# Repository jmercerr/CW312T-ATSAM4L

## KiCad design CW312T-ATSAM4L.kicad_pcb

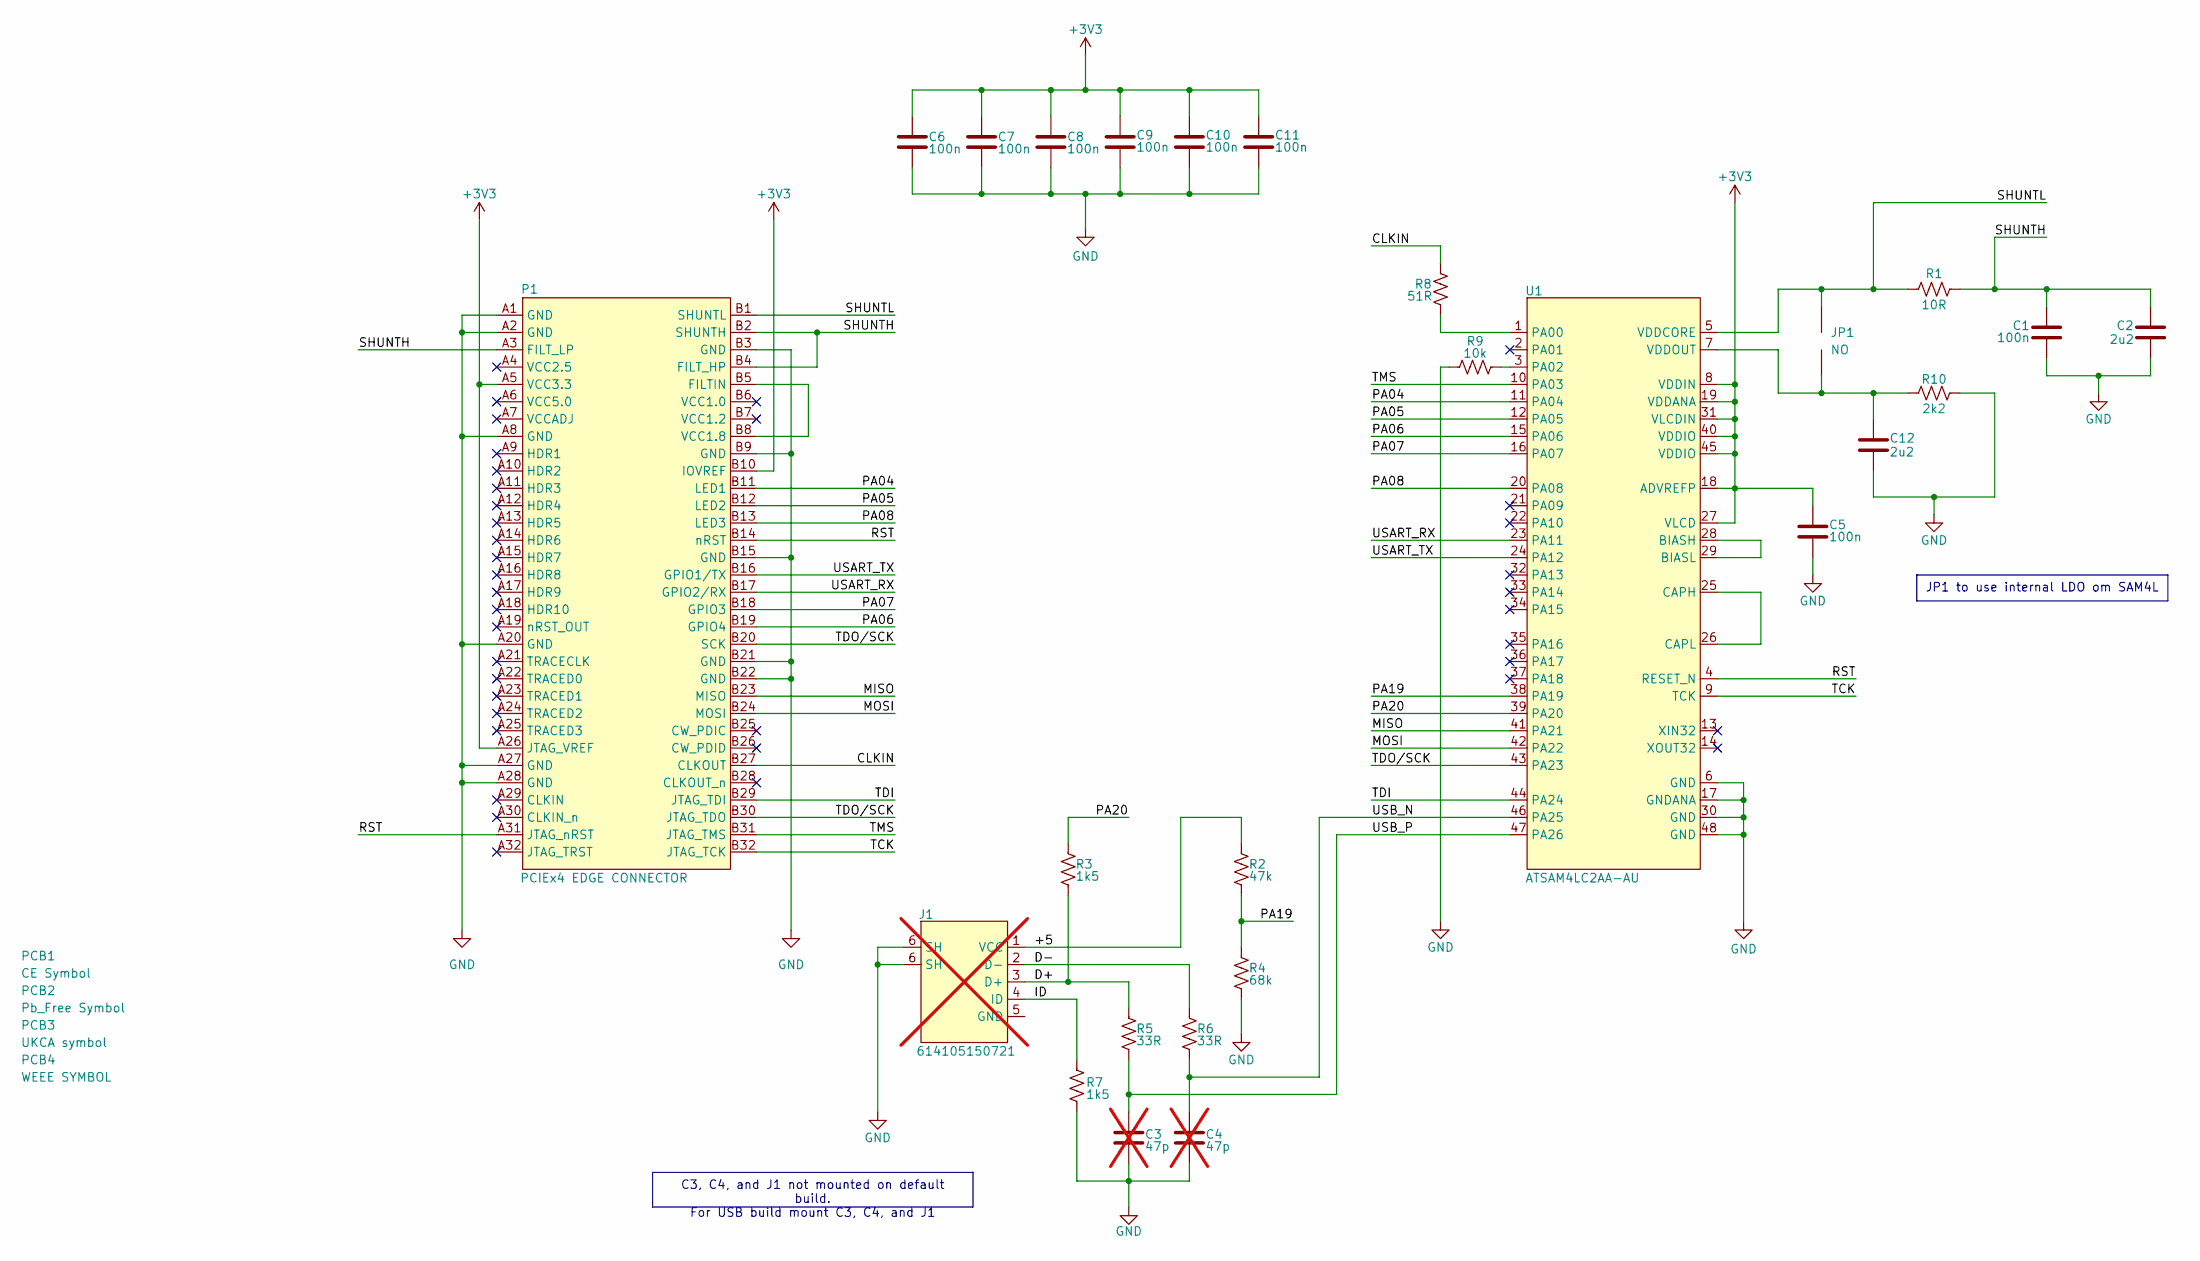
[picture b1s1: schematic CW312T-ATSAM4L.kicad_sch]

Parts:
C1, C5, C6, C7, C8, C9, C10, C11: CAP_100n_10V_0603; C_0603_1608Metric; Manufacturer Part Number CC0603KRX7R6BB104
C2, C12: CAP_2u2_6.3V_0603; C_0603_1608Metric; Manufacturer Part Number CC0603KRX7R5BB225
C3, C4: CAP_47p_50V_0603; C_0603_1608Metric; Manufacturer Part Number CC0603JRNPO9BN470; not fitted
J1: 614105150721; USB_Micro-B_Wuerth_614105150721_Vertical; Manufacturer Part Number 614105150721; not fitted
JP1: SolderJumper-2_P1.3mm_Open_Pad1.0x1.5mm
P1: PCIEx4 EDGE CONNECTOR; CW312_Template
PCB1: CE Symbol; CE-Logo_8.5x6mm_SilkScreen
PCB2: Pb_Free Symbol; Pb_Free_8.0x8.0mm_SilkScreen
PCB3: UKCA symbol; UKCA-Logo_8x8mm_SilkScreen
PCB4: WEEE SYMBOL; WEEE-Logo_5.6x8mm_SilkScreen
R1: RES_10R_0603; R_0603_1608Metric; Manufacturer Part Number RC0603FR-0710RL
R2: RES_47k_0603; R_0603_1608Metric; Manufacturer Part Number RC0603FR-0747KL
R3, R7: RES_1k5_0603; R_0603_1608Metric; Manufacturer Part Number RC0603FR-071K5L
R4: RES_68k_0603; R_0603_1608Metric; Manufacturer Part Number RC0603FR-0768KL
R5, R6: RES_33R_0603; R_0603_1608Metric; Manufacturer Part Number RC0603FR-0733RL
R8: RES_51R_0603; R_0603_1608Metric; Manufacturer Part Number RC0603FR-0751RL
R9: RES_10k_0603; R_0603_1608Metric; Manufacturer Part Number RC0603FR-0710KL
R10: RES_2k2_0603; R_0603_1608Metric; Manufacturer Part Number RC0603FR-072K2L
U1: ATSAM4LC2AA-AU; LQFP-48_7x7mm_P0.5mm; Manufacturer Part Number ATSAM4LC2AA-AU

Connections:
+3V3: C5.2, C6.2, C7.2, C8.2, C9.2, C10.2, C11.2, P1.A5 (VCC3.3), P1.A26 (JTAG_VREF), P1.B10 (IOVREF), U1.8 (VDDIN), U1.18 (ADVREFP), U1.19 (VDDANA), U1.27 (VLCD), U1.31 (VLCDIN), U1.40 (VDDIO), U1.45 (VDDIO)
/+5: J1.1 (VCC), R2.2
/CLKIN: P1.B27 (CLKOUT), R8.2
/D+: J1.3 (D+), R3.1, R5.2
/D-: J1.2 (D-), R6.2
/ID: J1.4 (ID), R7.2
/MISO: P1.B23 (MISO), U1.41 (PA21)
/MOSI: P1.B24 (MOSI), U1.42 (PA22)
/PA04: P1.B11 (LED1), U1.11 (PA04)
/PA05: P1.B12 (LED2), U1.12 (PA05)
/PA06: P1.B19 (GPIO4), U1.15 (PA06)
/PA07: P1.B18 (GPIO3), U1.16 (PA07)
/PA08: P1.B13 (LED3), U1.20 (PA08)
/PA19: R2.1, R4.2, U1.38 (PA19)
/PA20: R3.2, U1.39 (PA20)
/RST: P1.A31 (JTAG_nRST), P1.B14 (nRST), U1.4 (RESET_N)
/SHUNTH: C1.2, C2.1, P1.A3 (FILT_LP), P1.B2 (SHUNTH), P1.B4 (FILT_HP), R1.2
/SHUNTL: JP1.2, P1.B1 (SHUNTL), R1.1, U1.5 (VDDCORE)
/TCK: P1.B32 (JTAG_TCK), U1.9 (TCK)
/TDI: P1.B29 (JTAG_TDI), U1.44 (PA24)
/TDO/SCK: P1.B20 (SCK), P1.B30 (JTAG_TDO), U1.43 (PA23)
/TMS: P1.B31 (JTAG_TMS), U1.10 (PA03)
/USART_RX: P1.B17 (GPIO2/RX), U1.23 (PA11)
/USART_TX: P1.B16 (GPIO1/TX), U1.24 (PA12)
/USB_N: C4.2, R6.1, U1.46 (PA25)
/USB_P: C3.2, R5.1, U1.47 (PA26)
GND: C1.1, C2.2, C3.1, C4.1, C5.1, C6.1, C7.1, C8.1, C9.1, C10.1, C11.1, C12.2, J1.6 (SH), P1.A1 (GND), P1.A2 (GND), P1.A8 (GND), P1.A20 (GND), P1.A27 (GND), P1.A28 (GND), P1.B3 (GND), P1.B9 (GND), P1.B15 (GND), P1.B21 (GND), P1.B22 (GND), R4.1, R7.1, R9.1, R10.2, U1.6 (GND), U1.17 (GNDANA), U1.30 (GND), U1.48 (GND)
unnamed: P1.B5 (FILTIN), P1.B8 (VCC1.8)
unnamed: U1.28 (BIASH), U1.29 (BIASL)
unnamed: U1.25 (CAPH), U1.26 (CAPL)
unnamed: R8.1, U1.1 (PA00)
unnamed: R9.2, U1.3 (PA02)
unnamed: C12.1, JP1.1, R10.1, U1.7 (VDDOUT)

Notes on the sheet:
JP1 to use internal LDO om SAM4L
C3, C4, and J1 not mounted on default build. For USB build mount C3, C4, and J1

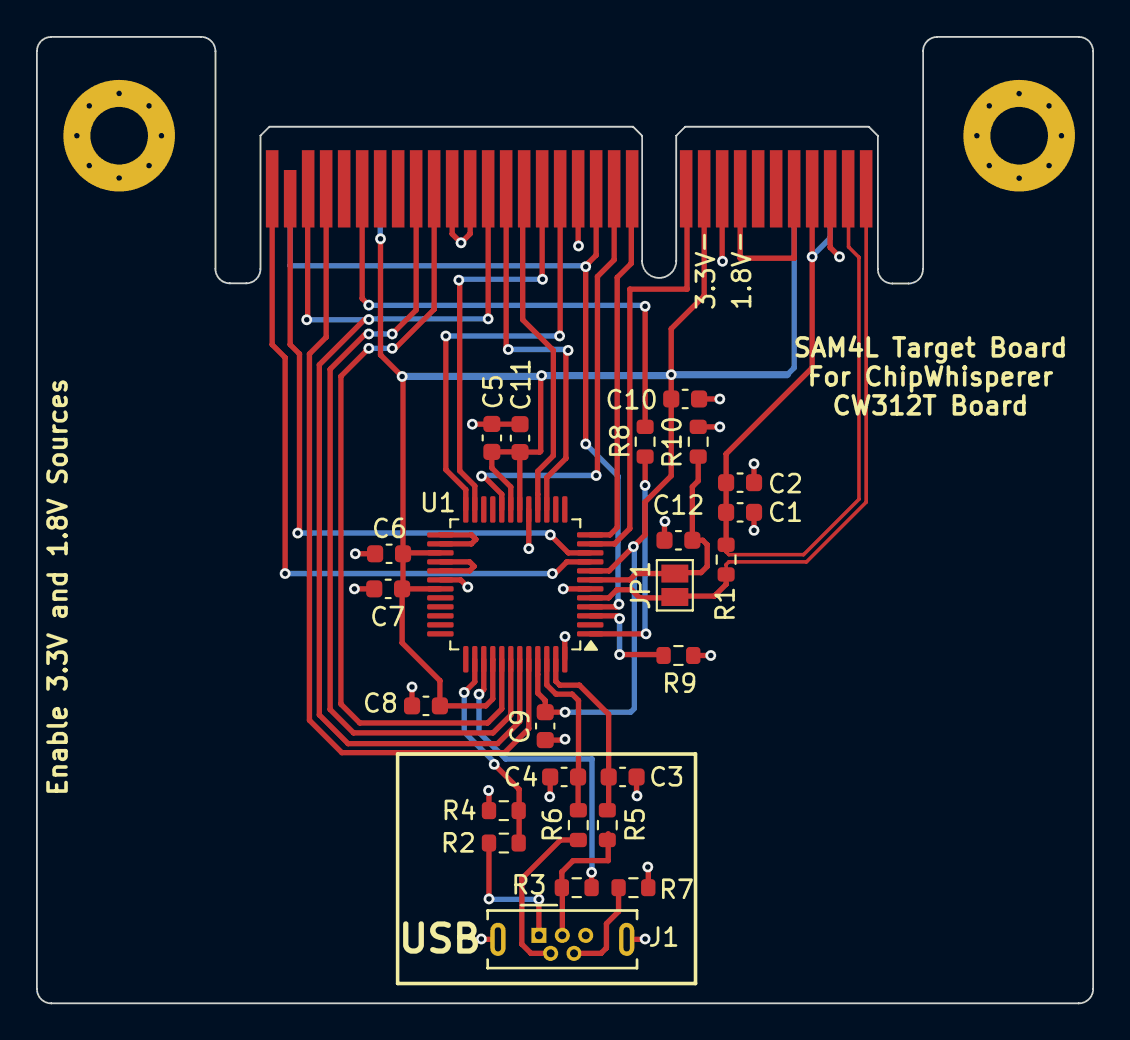
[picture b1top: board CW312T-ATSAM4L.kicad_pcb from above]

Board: 2 copper layers, 58.7 x 53.7 mm, 30 parts (0 on the bottom side), 33 nets.

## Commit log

2024-11-29 first draft - ready for review
2024-12-04 updated schematic, pcb, and production files - ready for review
2024-12-04 updated silkscreen, schematic notes, and production files
2024-12-19 updated schematic and pcb after library re-organization
